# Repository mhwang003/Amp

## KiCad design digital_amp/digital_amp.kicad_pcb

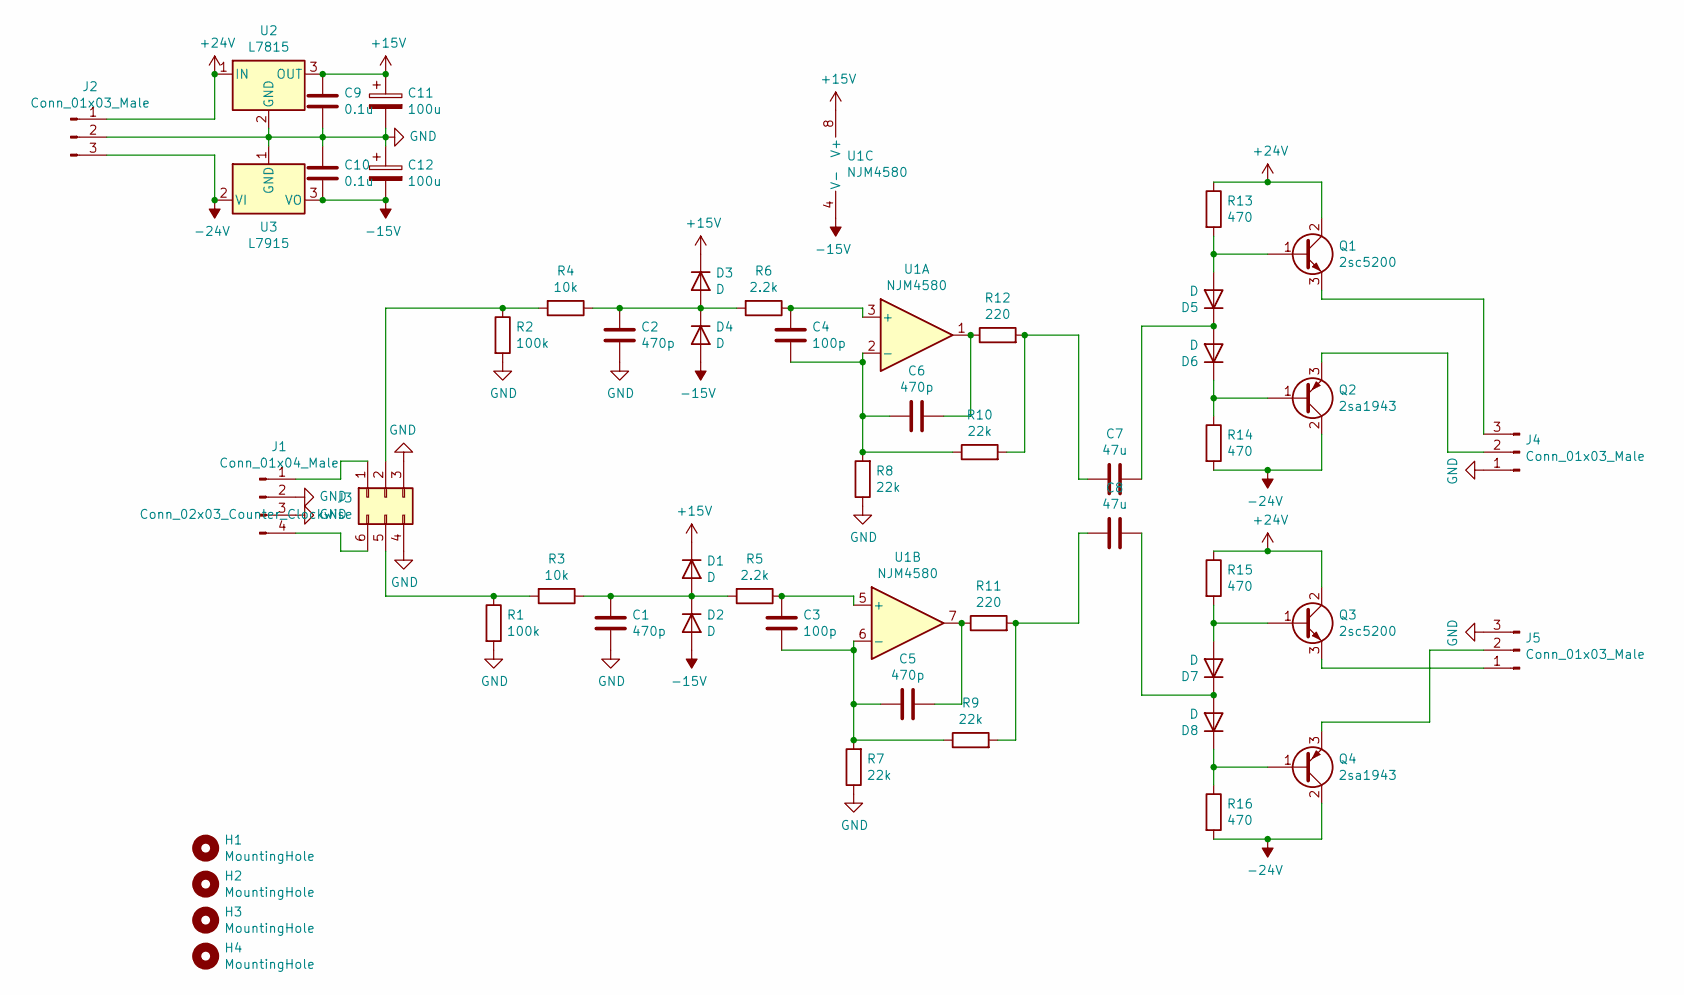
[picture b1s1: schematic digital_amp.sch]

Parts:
C1, C2, C5, C6: 470p; C_Disc_D4.3mm_W1.9mm_P5.00mm
C3, C4: 100p; C_Radial_D8.0mm_H7.0mm_P3.50mm
C7, C8: 47u; C_Radial_D6.3mm_H5.0mm_P2.50mm
C9, C10: 0.1u; C_Disc_D3.0mm_W1.6mm_P2.50mm
C11, C12: 100u; CP_Radial_D10.0mm_P5.00mm
D1, D2, D3, D4, D5, D6, D7, D8: D; D_T-1_P5.08mm_Horizontal
H1, H2, H3, H4: MountingHole; MountingHole_3.2mm_M3
J1: Conn_01x04_Male; PinHeader_1x04_P2.54mm_Vertical
J2, J4, J5: Conn_01x03_Male; JST_NV_B03P-NV_1x03_P5.00mm_Vertical
J3: Conn_02x03_Counter_Clockwise; PinSocket_1x06_P2.54mm_Vertical
Q1, Q3: 2sc5200; TO-3P-3_Horizontal_TabDown
Q2, Q4: 2sa1943; TO-3P-3_Horizontal_TabDown
R1, R2: 100k; R_Axial_DIN0204_L3.6mm_D1.6mm_P7.62mm_Horizontal
R3, R4: 10k; R_Axial_DIN0204_L3.6mm_D1.6mm_P7.62mm_Horizontal
R5, R6: 2.2k; R_Axial_DIN0204_L3.6mm_D1.6mm_P7.62mm_Horizontal
R7, R8, R9, R10: 22k; R_Axial_DIN0204_L3.6mm_D1.6mm_P7.62mm_Horizontal
R11, R12: 220; R_Axial_DIN0204_L3.6mm_D1.6mm_P7.62mm_Horizontal
R13, R14, R15, R16: 470; R_Axial_DIN0204_L3.6mm_D1.6mm_P7.62mm_Horizontal
U1: NJM4580; DIP-8_W7.62mm
U2: L7815; TO-220F-3_Horizontal_TabDown
U3: L7915; TO-220F-3_Horizontal_TabDown

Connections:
+15V: C9.1, C11.1, D1.1 (K), D3.1 (K), U1.8 (V+), U2.3 (OUT)
+24V: J2.1, Q1.2 (C), Q3.2 (C), R13.1, R15.1, U2.1 (IN)
-15V: C10.2, C12.2, D2.2 (A), D4.2 (A), U1.4 (V-), U3.3 (VO)
-24V: J2.3, Q2.2 (C), Q4.2 (C), R14.2, R16.2, U3.2 (VI)
GND: C1.2, C2.2, C9.2, C10.1, C11.2, C12.1, J1.2, J1.3, J2.2, J3.3, J3.4, J4.1, J5.3, R1.2, R2.2, R7.1, R8.1, U2.2 (GND), U3.1 (GND)
unnamed: C1.1, D1.2 (A), D2.1 (K), R3.1, R5.2
unnamed: C2.1, D3.2 (A), D4.1 (K), R4.1, R6.2
unnamed: C3.1, C5.2, R7.2, R9.1, U1.6 (-)
unnamed: C3.2, R5.1, U1.5 (+)
unnamed: C4.1, C6.2, R8.2, R10.1, U1.2 (-)
unnamed: C4.2, R6.1, U1.3 (+)
unnamed: C5.1, R11.1, U1.7
unnamed: C6.1, R12.1, U1.1
unnamed: C7.1, D5.1 (K), D6.2 (A)
unnamed: C7.2, R10.2, R12.2
unnamed: C8.1, D7.1 (K), D8.2 (A)
unnamed: C8.2, R9.2, R11.2
unnamed: D5.2 (A), Q1.1 (B), R13.2
unnamed: D6.1 (K), Q2.1 (B), R14.1
unnamed: D7.2 (A), Q3.1 (B), R15.2
unnamed: D8.1 (K), Q4.1 (B), R16.1
unnamed: J1.1, J3.1
unnamed: J1.4, J3.6
unnamed: J3.2, R2.1, R4.2
unnamed: J3.5, R1.1, R3.2
unnamed: J4.2, Q2.3 (E)
unnamed: J4.3, Q1.3 (E)
unnamed: J5.1, Q3.3 (E)
unnamed: J5.2, Q4.3 (E)

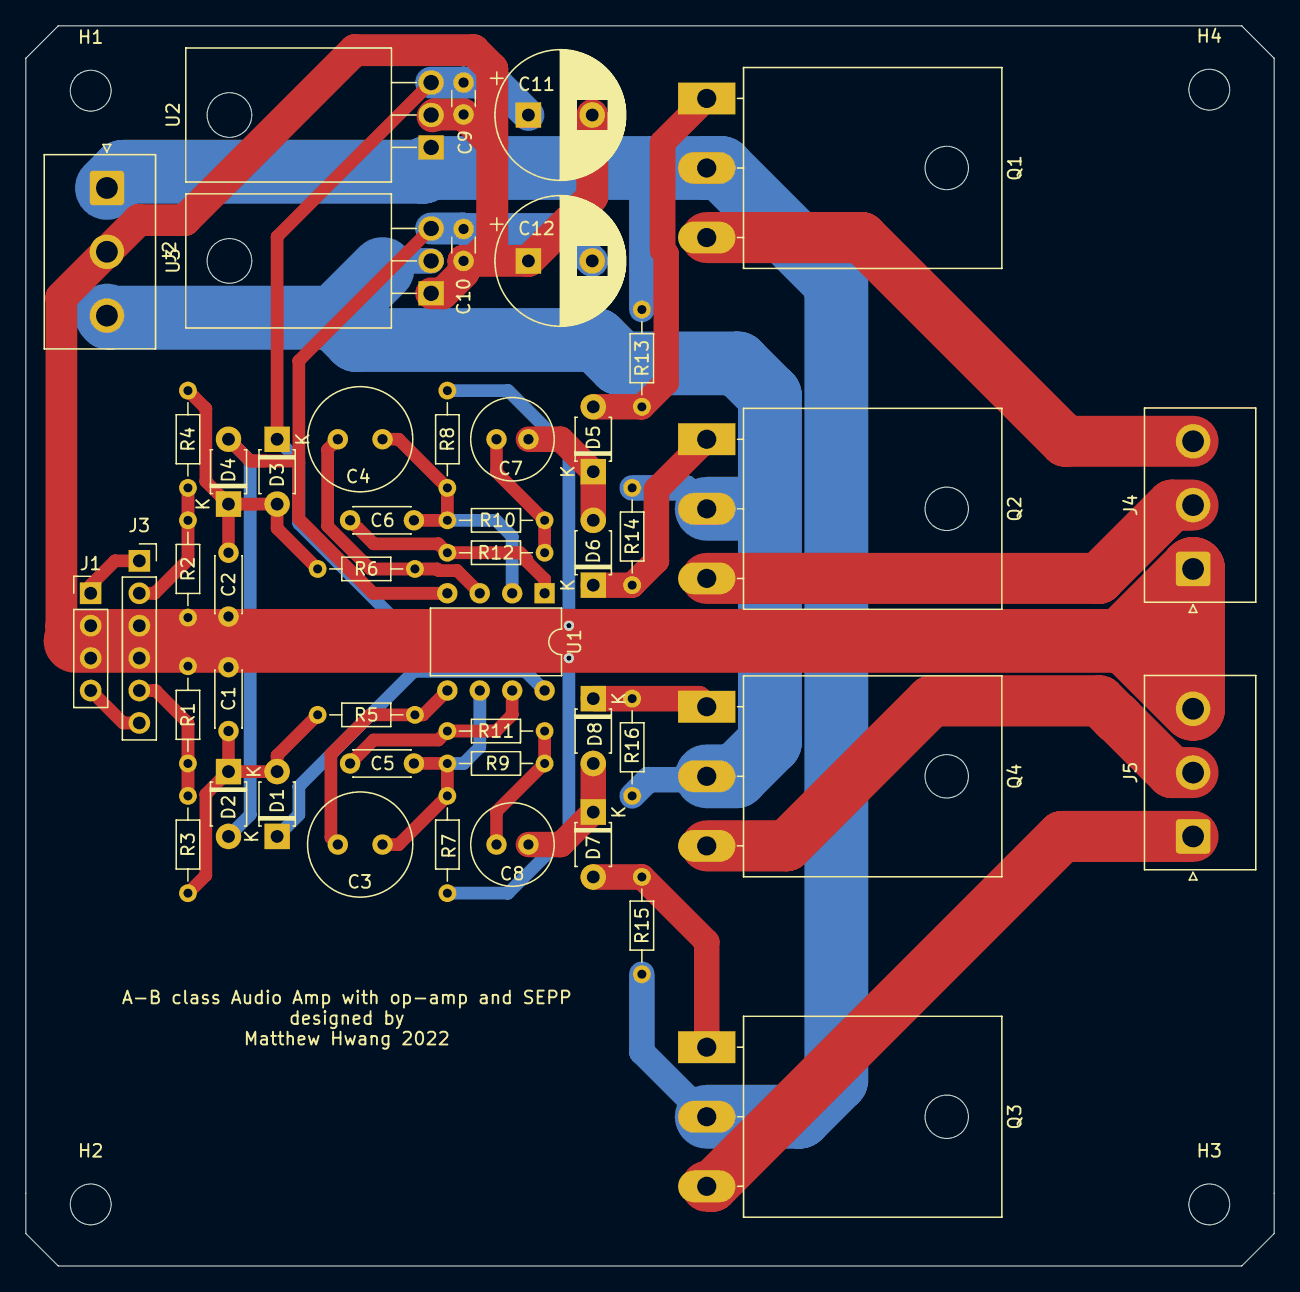
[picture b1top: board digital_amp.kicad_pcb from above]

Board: 2 copper layers, 97.8 x 97.2 mm, 52 parts (0 on the bottom side), 29 nets.

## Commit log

2022-04-09 added files including kicad project
